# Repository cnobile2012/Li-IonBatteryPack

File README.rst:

*******************
Li-Ion Battery Pack
*******************
The MIT License (MIT)

This circuit board provides the ability to manage 3 to 5 Li-Ion batteries with the BMS at this link.
`BMS Board <https://www.banggood.com/3S-4S-5S-Bms-12v-16_8V-21V-3_7V-100A-Li-ion-Lmo-Ternary-Lithium-Battery-Protection-Circuit-Board-Li-polymer-Balance-Charging-p-1834472.html?cur_warehouse=CN&ID=63059756294209&rmmds=category>`_

These are the BMS boards used:

.. image:: images/5S-BMS-Frontside.jpg
  :width: 400
  :alt: BMS Frontside image

.. image:: images/5S-BMS-Backside.jpg
  :width: 400
  :alt: BMS Backside image

Version 1.0 of the circuit board:

.. image:: images/Li-IonBatteryPack-Frontside.jpg
  :width: 400
  :alt: Circuit board Frontside image

.. image:: images/Li-IonBatteryPack-Backside.jpg
  :width: 400
  :alt: Circuit board Backside image

=====
KiCAD
=====

KiCAD files of the schematic and PCB.

Feel free to contact me at: carl dot nobile at gmail.com

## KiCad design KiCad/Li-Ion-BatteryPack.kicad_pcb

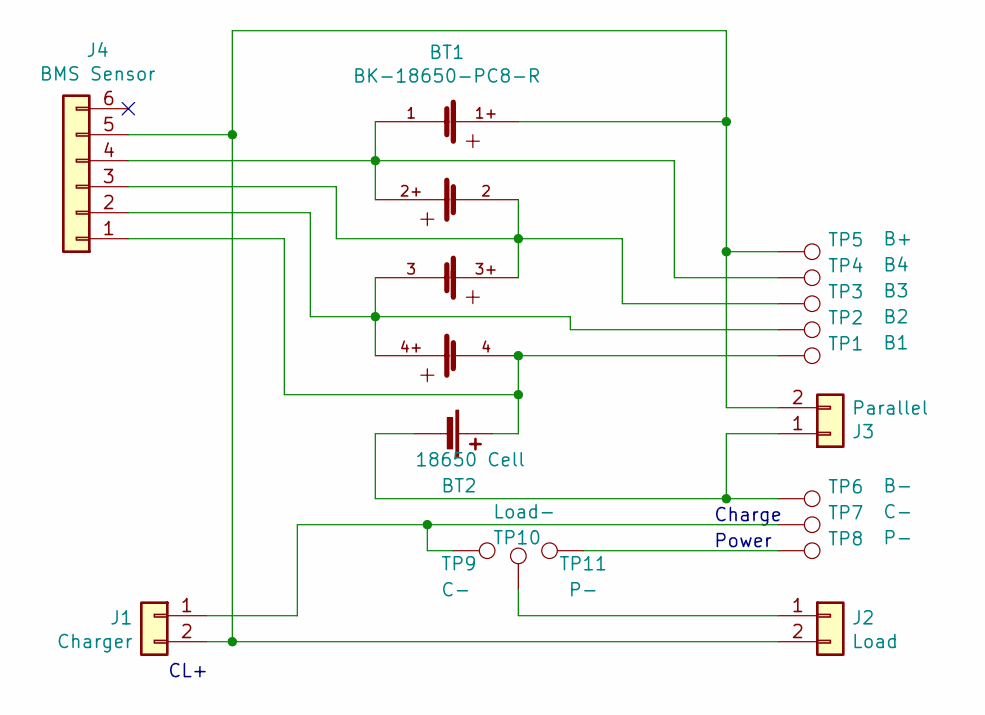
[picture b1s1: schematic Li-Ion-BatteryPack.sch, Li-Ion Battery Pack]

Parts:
BT1: BK-18650-PC8-R; BAT_BK-18650-PC8-R; PARTREV L
BT2: 18650 Cell; BatteryHolder_MPD_BH-18650-PC2
J1: Charger; AMASS_XT60-M_1x02_P7.20mm_Vertical
J2: Load; AMASS_XT60-F_1x02_P7.20mm_Vertical
J3: Parallel; AMASS_XT60-F_1x02_P7.20mm_Vertical
J4: BMS Sensor; PinHeader_1x06_P2.54mm_Vertical
TP1: B1; Pin_D1.1mm_L8.5mm_W2.5mm_FlatFork
TP2: B2; Pin_D1.1mm_L8.5mm_W2.5mm_FlatFork
TP3: B3; Pin_D1.1mm_L8.5mm_W2.5mm_FlatFork
TP4: B4; Pin_D1.1mm_L8.5mm_W2.5mm_FlatFork
TP5: B+; Pin_D1.1mm_L8.5mm_W2.5mm_FlatFork
TP6: B-; Pin_D1.3mm_L10.0mm_W3.5mm_Flat
TP7, TP9: C-; Pin_D1.3mm_L10.0mm_W3.5mm_Flat
TP8, TP11: P-; Pin_D1.3mm_L10.0mm_W3.5mm_Flat
TP10: Load-; Pin_D1.3mm_L10.0mm_W3.5mm_Flat

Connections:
unnamed: BT1.1, BT1.2+, J4.4, TP4.1
unnamed: BT1.1+, J1.2, J2.2, J3.2, J4.5, TP5.1
unnamed: BT1.2, BT1.3+, J4.3, TP3.1
unnamed: BT1.3, BT1.4+, J4.2, TP2.1
unnamed: BT1.4, BT2.1 (+), J4.1, TP1.1
unnamed: BT2.2 (-), J3.1, TP6.1
unnamed: J1.1, TP7.1, TP9.1
unnamed: J2.1, TP10.1
unnamed: TP8.1, TP11.1

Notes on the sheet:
CL+
Charge
Power

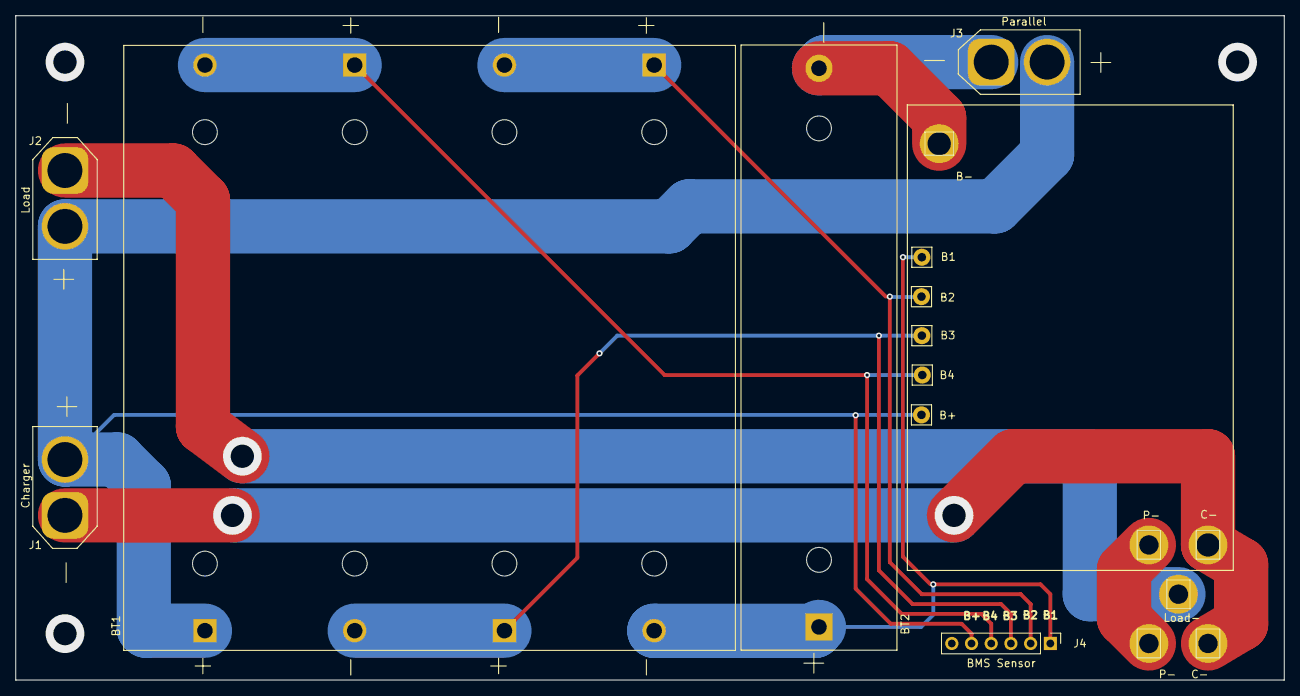
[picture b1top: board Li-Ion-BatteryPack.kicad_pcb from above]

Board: 2 copper layers, 163.5 x 85.6 mm, 17 parts (0 on the bottom side), 9 nets.

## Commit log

2021-06-16 Initial commit.
2021-06-16 Added images to the README.
2021-06-16 Updates on gerber files.
2021-06-16 Flipped the image.
2021-06-16 Removed a huge cache file that KiCAD will rebuild.
2021-06-16 Updated the gerber files.
2021-06-24 Added circuit board images.
2021-06-24 Added some silkscreen objects to give better hints on wirering.
2021-06-24 Fixed a spelling error.
2021-06-25 Flipped some high current connections to the back of the board.
2021-07-21 Fixed spelling mistakes in the images alt text.
